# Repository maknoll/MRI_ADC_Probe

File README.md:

# STIMULATE MRI ADC Probe

This repository includes all hard- firm- and software resources realated to MRI ADC Probe developed for measuring gradient fields in a running MRI scanner. It is theoretically possible to sample 4 channels at 4.8Msps, however, at the moment it is limited to 2 channels at 200ksps due to bandwith limitations. Data is transmitted out of the MRI by consumer TOSLINK transmitters and optical fibre cable. 

## Hardware

The sampling Device is a STM32F303CCT6 ARM Cortex-M4 microprocessor. It was chosen for its 4 integrated operational Amplifiers, configured for offsetting, amplifying and buffering the input signals. It also features 4 high speed ADCs, multiple DMA channels and a DSP-like instruction set.

## Firmware

The firmware is inteded to sample continiusly, copy the samples from the ADCs to buffers with DMA and push them out of the UART as fast as possible.

## Software

The software receives data through a high-speed FT2232H USB Serial Interface and decodes the channels using a state machine. Samples for each channel are written to there subsequent files.

## Installation

### Dependencies

Developement machines should be configured with:

- libFTDI > 1.0
- a arm-none-eabi toolchain with gdb
- Eclipse
- the gnuarmeclipse plugin
- the STM32CubeMX eclipse plugin
- Kicad > 4.0, if hardware needs to be modified

### Setup

_The gnuarmeclipse Environment might has to be configured. This should be easiest by first creating a dummy project following the tutotials and making sure it works before continuing._

Import projects into Eclipse using the "Import -> Existing Projects into Workspace" Dialog.

The project template generator STM32CubeMX can be used directly from Eclipse by opening the firmware.ioc file. It is however standalone Software and has to be configured seperately to output generated code into the _firmware_ folder. This might or might not be the case after installation.

The Kicad project is opened by simply loading the ADC.pro file.

## Usage

If the probe is connected to the antennas and powered with ~5V, it outputs samples continously. To read and save them, the software has to be started on the host connected to the FT223H via USB. Filename prefixes can be chosen with the -f option. The software is stopped by hitting ctr-c.

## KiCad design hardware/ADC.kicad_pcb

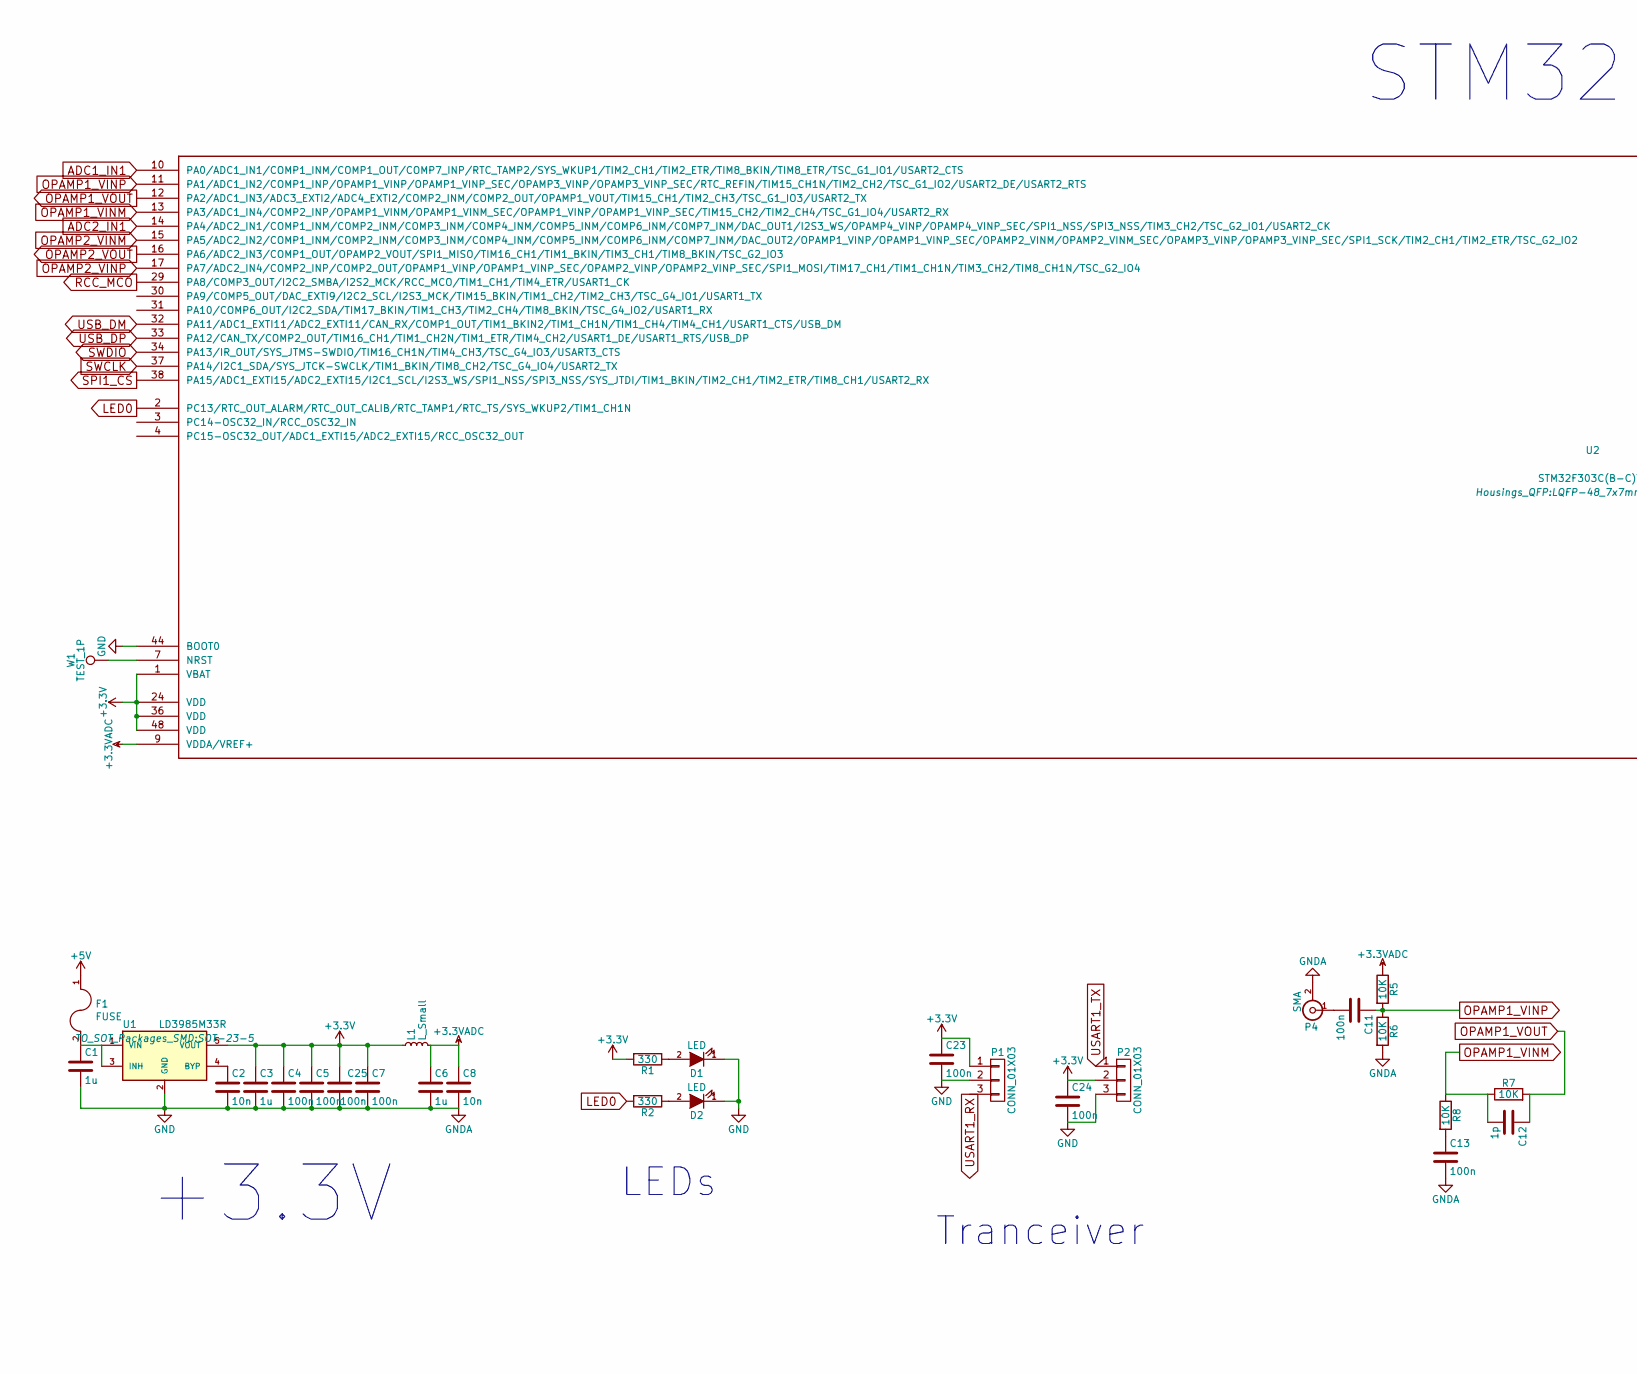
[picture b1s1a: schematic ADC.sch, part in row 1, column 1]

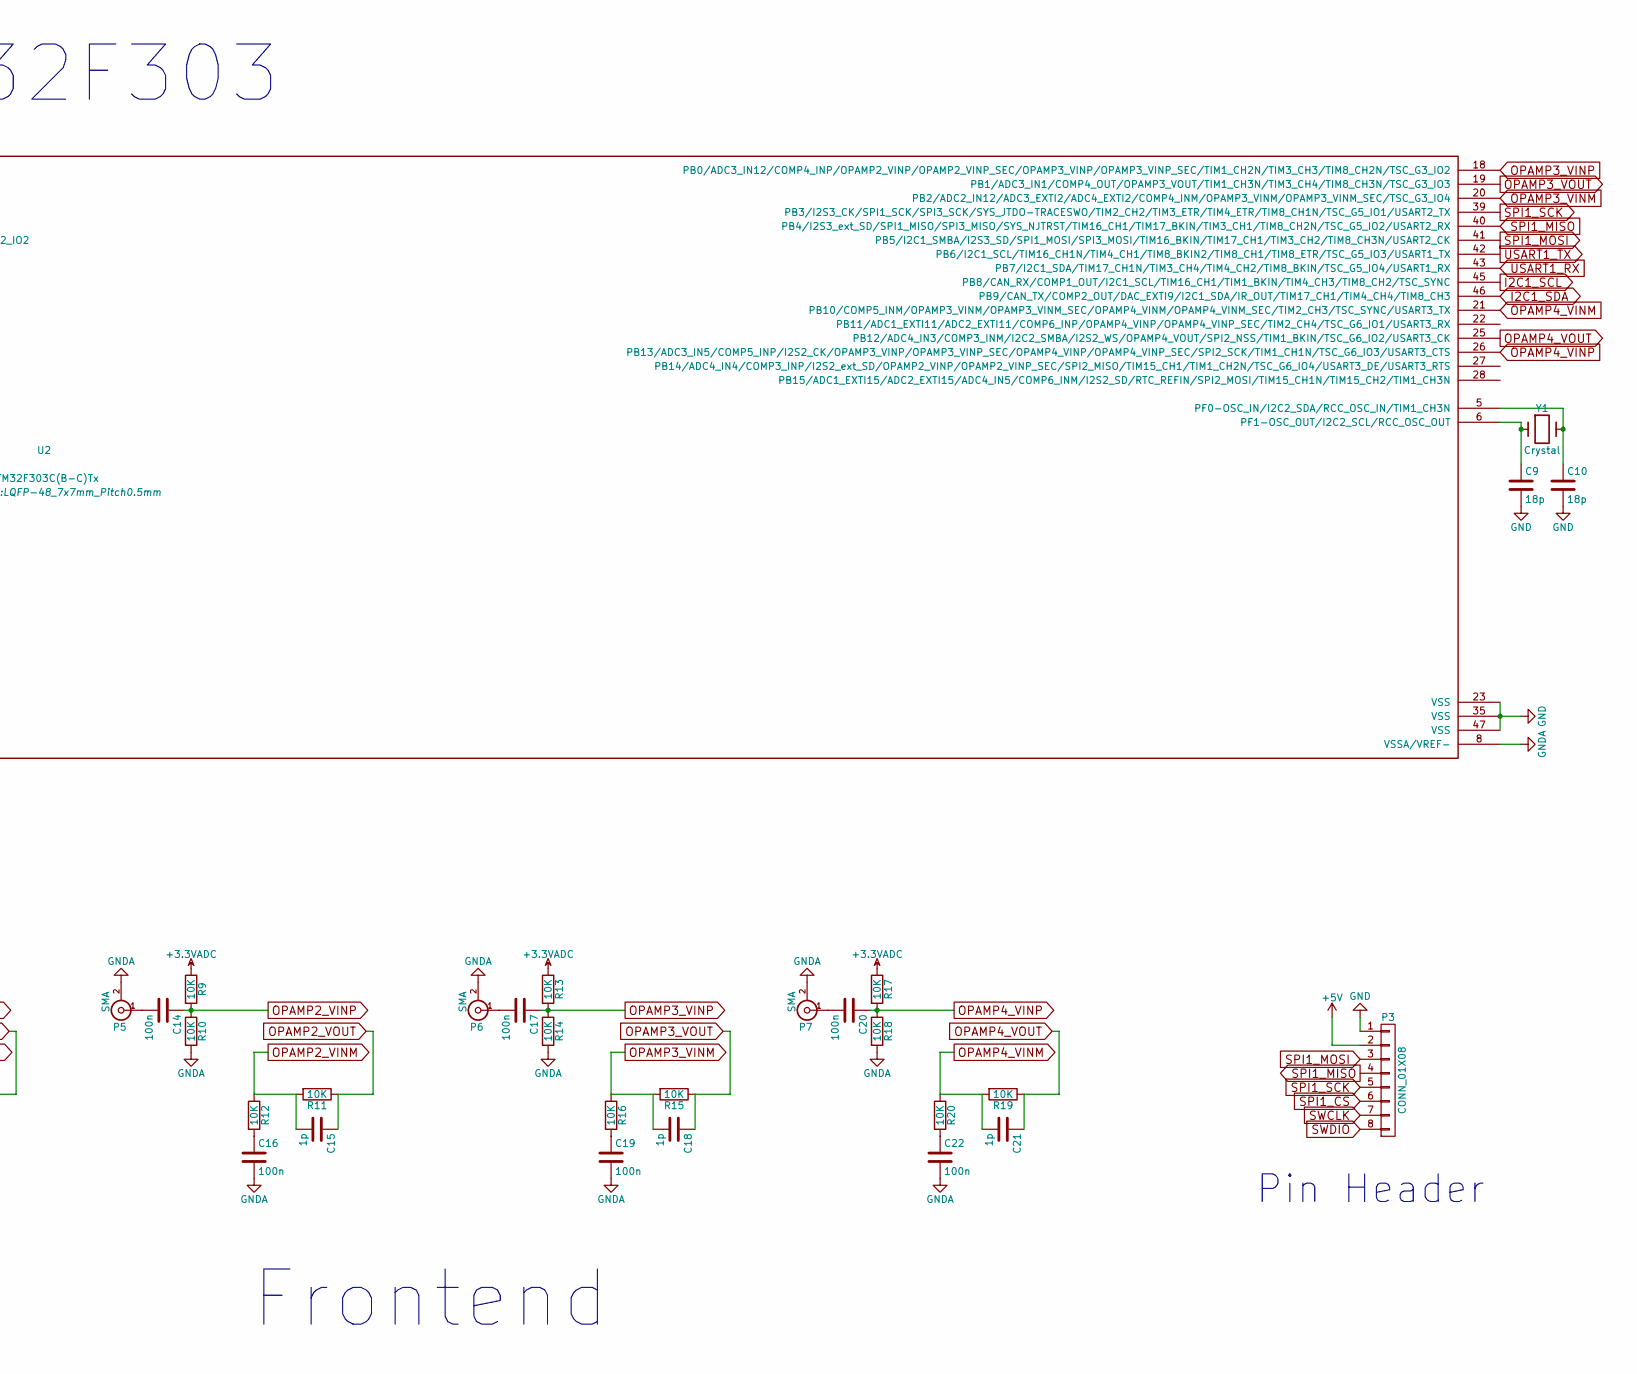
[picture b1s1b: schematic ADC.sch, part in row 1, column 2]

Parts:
C1, C3, C6: 1u; C_0603
C2, C8: 10n; C_0603
C4, C5, C7, C11, C13, C14, C16, C17, C19, C20, C22, C23, C24, C25: 100n; C_0603
C9, C10: 18p; C_0603
C12, C15, C18, C21: 1p; C_0603
D1, D2: LED; LED_0603
F1: FUSE; Fuse_SMD1206_Reflow
L1: L_Small; R_0603
P1, P2: CONN_01X03; Toslink Tranceiver
P3: CONN_01X08; Pin_Header_Straight_1x08
P4, P5, P6, P7: SMA; SMA-ThroughHole
R1, R2: 330; R_0603
R5, R6, R7, R8, R9, R10, R11, R12, R13, R14, R15, R16, R17, R18, R19, R20: 10K; R_0603
U1: LD3985M33R; SOT-23-5; Part Number LD3985M33R
U2: STM32F303C(B-C)Tx; LQFP-48_7x7mm_Pitch0.5mm; Part Number STM32F303CCT6
W1: TEST_1P; Measurement_Point_Round-SMD-Pad_Small
Y1: Crystal; ABM3

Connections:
+3.3VADC: C6.1, C8.1, L1.2, R5.1, R9.1, R13.1, R17.1, U2.9 (VDDA/VREF+)
+3V3: C3.1, C4.1, C5.1, C7.1, C23.1, C24.1, C25.1, L1.1, P1.1, P2.2, R1.2, U1.5 (VOUT), U2.1 (VBAT), U2.24 (VDD), U2.36 (VDD), U2.48 (VDD)
+5V: F1.1, P3.2
ADC1_IN1: U2.10 (PA0/ADC1_IN1/COMP1_INM/COMP1_OUT/COMP7_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)
ADC2_IN1: U2.14 (PA4/ADC2_IN1/COMP1_INM/COMP2_INM/COMP3_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)
GND: C1.2, C2.2, C3.2, C4.2, C5.2, C6.2, C7.2, C8.2, C9.2, C10.2, C13.2, C16.2, C19.2, C22.2, C23.2, C24.2, C25.2, D1.1 (K), D2.1 (K), P1.2, P2.3, P3.1, P4.2 (Ext), P5.2 (Ext), P6.2 (Ext), P7.2 (Ext), R6.2, R10.2, R14.2, R18.2, U1.2 (GND), U2.8 (VSSA/VREF-), U2.23 (VSS), U2.35 (VSS), U2.44 (BOOT0), U2.47 (VSS)
I2C1_SCL: U2.45 (PB8/CAN_RX/COMP1_OUT/I2C1_SCL/TIM16_CH1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)
I2C1_SDA: U2.46 (PB9/CAN_TX/COMP2_OUT/DAC_EXTI9/I2C1_SDA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)
LED0: R2.2, U2.2 (PC13/RTC_OUT_ALARM/RTC_OUT_CALIB/RTC_TA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)
unnamed: C1.1, F1.2, U1.1 (VIN), U1.3 (INH)
unnamed: C2.1, U1.4 (BYP)
unnamed: C9.1, U2.6 (PF1-OSC_OUT/I2C2_SCL/RCC_OSC_OUT), Y1.1
unnamed: C10.1, U2.5 (PF0-OSC_IN/I2C2_SDA/RCC_OSC_IN/TIM1_CH3N), Y1.2
unnamed: C11.2, P4.1 (In)
unnamed: C13.1, R8.2
unnamed: C14.2, P5.1 (In)
unnamed: C16.1, R12.2
unnamed: C17.2, P6.1 (In)
unnamed: C19.1, R16.2
unnamed: C20.2, P7.1 (In)
unnamed: C22.1, R20.2
unnamed: D1.2 (A), R1.1
unnamed: D2.2 (A), R2.1
unnamed: U2.7 (NRST), W1.1
OPAMP1_VINM: C12.2, R7.1, R8.1, U2.13 (PA3/ADC1_IN4/COMP2_INP/OPAMP1_VINM/OPAM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)
OPAMP1_VINP: C11.1, R5.2, R6.1, U2.11 (PA1/ADC1_IN2/COMP1_INP/OPAMP1_VINP/OPAM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)
OPAMP1_VOUT: C12.1, R7.2, U2.12 (PA2/ADC1_IN3/ADC3_EXTI2/ADC4_EXTI2/COMP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)
OPAMP2_VINM: C15.2, R11.2, R12.1, U2.15 (PA5/ADC2_IN2/COMP1_INM/COMP2_INM/COMP3_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)
OPAMP2_VINP: C14.1, R9.2, R10.1, U2.17 (PA7/ADC2_IN4/COMP2_INP/COMP2_OUT/OPAMP1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)
OPAMP2_VOUT: C15.1, R11.1, U2.16 (PA6/ADC2_IN3/COMP1_OUT/OPAMP2_VOUT/SPI1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)
OPAMP3_VINM: C18.2, R15.2, R16.1, U2.20 (PB2/ADC2_IN12/ADC3_EXTI2/ADC4_EXTI2/COM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)
OPAMP3_VINP: C17.1, R13.2, R14.1, U2.18 (PB0/ADC3_IN12/COMP4_INP/OPAMP2_VINP/OPA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)
OPAMP3_VOUT: C18.1, R15.1, U2.19 (PB1/ADC3_IN1/COMP4_OUT/OPAMP3_VOUT/TIM1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)
OPAMP4_VINM: C21.2, R19.2, R20.1, U2.21 (PB10/COMP5_INM/OPAMP3_VINM/OPAMP3_VINM_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)
OPAMP4_VINP: C20.1, R17.2, R18.1, U2.26 (PB13/ADC3_IN5/COMP5_INP/I2S2_CK/OPAMP3_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)
OPAMP4_VOUT: C21.1, R19.1, U2.25 (PB12/ADC4_IN3/COMP3_INM/I2C2_SMBA/I2S2_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)
RCC_MCO: U2.29 (PA8/COMP3_OUT/I2C2_SMBA/I2S2_MCK/RCC_MC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)
SPI1_CS: P3.6, U2.38 (PA15/ADC1_EXTI15/ADC2_EXTI15/I2C1_SCL/I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)
SPI1_MISO: P3.4, U2.40 (PB4/I2S3_ext_SD/SPI1_MISO/SPI3_MISO/SYS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)
SPI1_MOSI: P3.3, U2.41 (PB5/I2C1_SMBA/I2S3_SD/SPI1_MOSI/SPI3_MO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)
SPI1_SCK: P3.5, U2.39 (PB3/I2S3_CK/SPI1_SCK/SPI3_SCK/SYS_JTDO-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)
SWCLK: P3.7, U2.37 (PA14/I2C1_SDA/SYS_JTCK-SWCLK/TIM1_BKIN/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)
SWDIO: P3.8, U2.34 (PA13/IR_OUT/SYS_JTMS-SWDIO/TIM16_CH1N/T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)
USART1_RX: P1.3, U2.43 (PB7/I2C1_SDA/TIM17_CH1N/TIM3_CH4/TIM4_C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)
USART1_TX: P2.1, U2.42 (PB6/I2C1_SCL/TIM16_CH1N/TIM4_CH1/TIM8_B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)
USB_DM: U2.32 (PA11/ADC1_EXTI11/ADC2_EXTI11/CAN_RX/COM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)
USB_DP: U2.33 (PA12/CAN_TX/COMP2_OUT/TIM16_CH1/TIM1_CH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)

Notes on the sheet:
Frontend
+3.3V
Tranceiver
LEDs
STM32F303
Pin Header

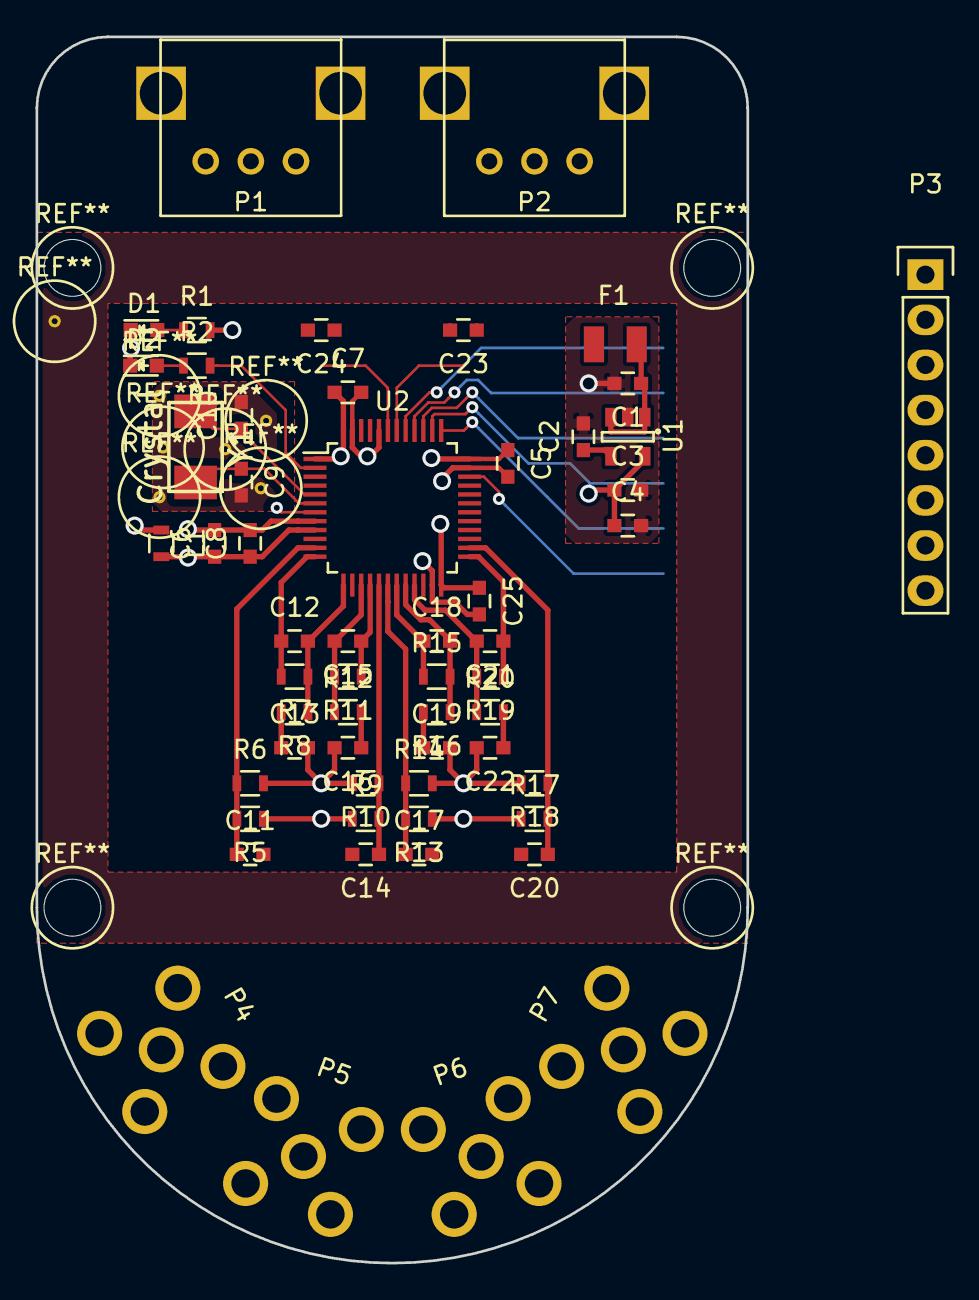
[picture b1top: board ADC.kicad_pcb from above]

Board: 4 copper layers, 40.0 x 69.0 mm, 58 parts (1 on the bottom side), 40 nets.

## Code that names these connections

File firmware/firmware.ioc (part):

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Mcu.Name=STM32F303C(B-C)Tx
Mcu.Package=LQFP48
Mcu.UserName=STM32F303CCTx
PA1.Mode=Standalone
PA1.Signal=OPAMP1_VINP
PA13.Mode=Serial-Wire
PA13.Signal=SYS_JTMS-SWDIO
PA14.Mode=Serial-Wire
PA14.Signal=SYS_JTCK-SWCLK
PA2.Mode=Standalone
PA2.Signal=OPAMP1_VOUT
PA3.Mode=Standalone
PA3.Signal=OPAMP1_VINM
PA5.Mode=Standalone
PA5.Signal=OPAMP2_VINM
PA6.Mode=Standalone
PA6.Signal=OPAMP2_VOUT
PA7.Mode=Standalone
PA7.Signal=OPAMP2_VINP
PB0.Mode=Standalone
PB0.Signal=OPAMP3_VINP
PB1.Mode=Standalone
PB1.Signal=OPAMP3_VOUT
PB10.Mode=Standalone
PB10.Signal=OPAMP4_VINM
PB12.Mode=Standalone
PB12.Signal=OPAMP4_VOUT
PB13.Mode=Standalone
PB13.Signal=OPAMP4_VINP
PB2.Mode=Standalone
PB2.Signal=OPAMP3_VINM
PB3.Mode=TX_Only_Simplex_Unidirect_Master
PB3.Signal=SPI1_SCK
PB5.Mode=TX_Only_Simplex_Unidirect_Master
PB5.Signal=SPI1_MOSI
PB6.Mode=Asynchronous
PB6.Signal=USART1_TX
PB7.Mode=Asynchronous
PB7.Signal=USART1_RX
PC13.Signal=GPIO_Output
PF0-OSC_IN.Mode=HSE-External-Oscillator
PF0-OSC_IN.Signal=RCC_OSC_IN
PF1-OSC_OUT.Mode=HSE-External-Oscillator
PF1-OSC_OUT.Signal=RCC_OSC_OUT
RCC.HSEPLLFreq_Value=8000000
RCC.HSE_VALUE=8000000
RCC.SYSCLKFreq_VALUE=64000000
RCC.SYSCLKSourceVirtual=RCC_SYSCLKSOURCE_PLLCLK
board=ADC
boardIOC=true

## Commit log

2016-05-13 reorganising project into one single repository
2016-05-26 error correction
2016-05-29 fixed host software error correction
2016-08-16 output error corrections to file
